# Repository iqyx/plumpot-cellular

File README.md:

plumpot-cellular
===================

A plumpot series base board with a sub-1GHz radio and a 2.5G cellular modem

Features
--------------------

- half-length, half-width form factor (80x50mm)
- mounting holes for half-length half-width and half-length quarter-width extension boards
- two extension bus connectors (UXB1 compatible - multidrop half-duplex SPI bus, I2C bus, wakeup request, interrupt request and 5V power)
- AX5243 sub-1GHz radio module with a 50ohm MMCX antenna connector
- Quectel M66 2.5G GPRS/EDGE cellular modem with a 50ohm MMCX antenna connector and network activity LED indicators
- 6-60Vin power supply step down regulator for providing system and bus power (5V, 0.2A)
- micro-B USB port with a CP2101 serial to USB bridge (console access and power input)
- RTC with a CR1220 lithium coin cell backup

The board is developed as an open source hardware using tools freely available for non-
commercial usage. It is able to run free and non-free commercial software without any
restrictions. It is not locked to a specific firmware and contains a standard 10-pin Cortex Debug
connector. A multitude of free and commercial development tools exist to develop and modify the
firmware for the board.

History
----------------

This is a uNodeX form-factor version of the qNode4 board (hence the previous name "unodex-connect-42").

I accepted a set of rules for board design, sizes, mounting types and board communication
to ease the development of new hardware. Such hardware could be easily connected together
to form wireless nodes for IoT/IoM and similar usages and enables you to do data acquisition,
data forwarding/communication, control, etc. I started to call this platform "uNodeX"
(micro node - extendable).

This is a rework of the previous qNode4 board to be compatible with the uNodeX platform,
with a slightly modified hardware:

- step-up converter for battery charging is removed
- RF connectors are changed to MMCX
- uNodeX bus connectors are added
- board dimensions are changed to 50x80mm (uNodeX half-width, half-depth)
- CP2102 USB to serial converter for console access
- VBUS power oring controller for uNodeX bus
- 6-60VDC step-down converter is added
- temperature sensor is removed

The board includes only a reduced set of hardware to fulfill the following requirements:

- to be a mainboard for HWHD or QWHD cards
- to provide power for them
- to enable them to communicate over the air (uMesh stack or GPRS/EDGE)

I started to call this board "plumpot" as it is mainly used to run the plumCore firmware.

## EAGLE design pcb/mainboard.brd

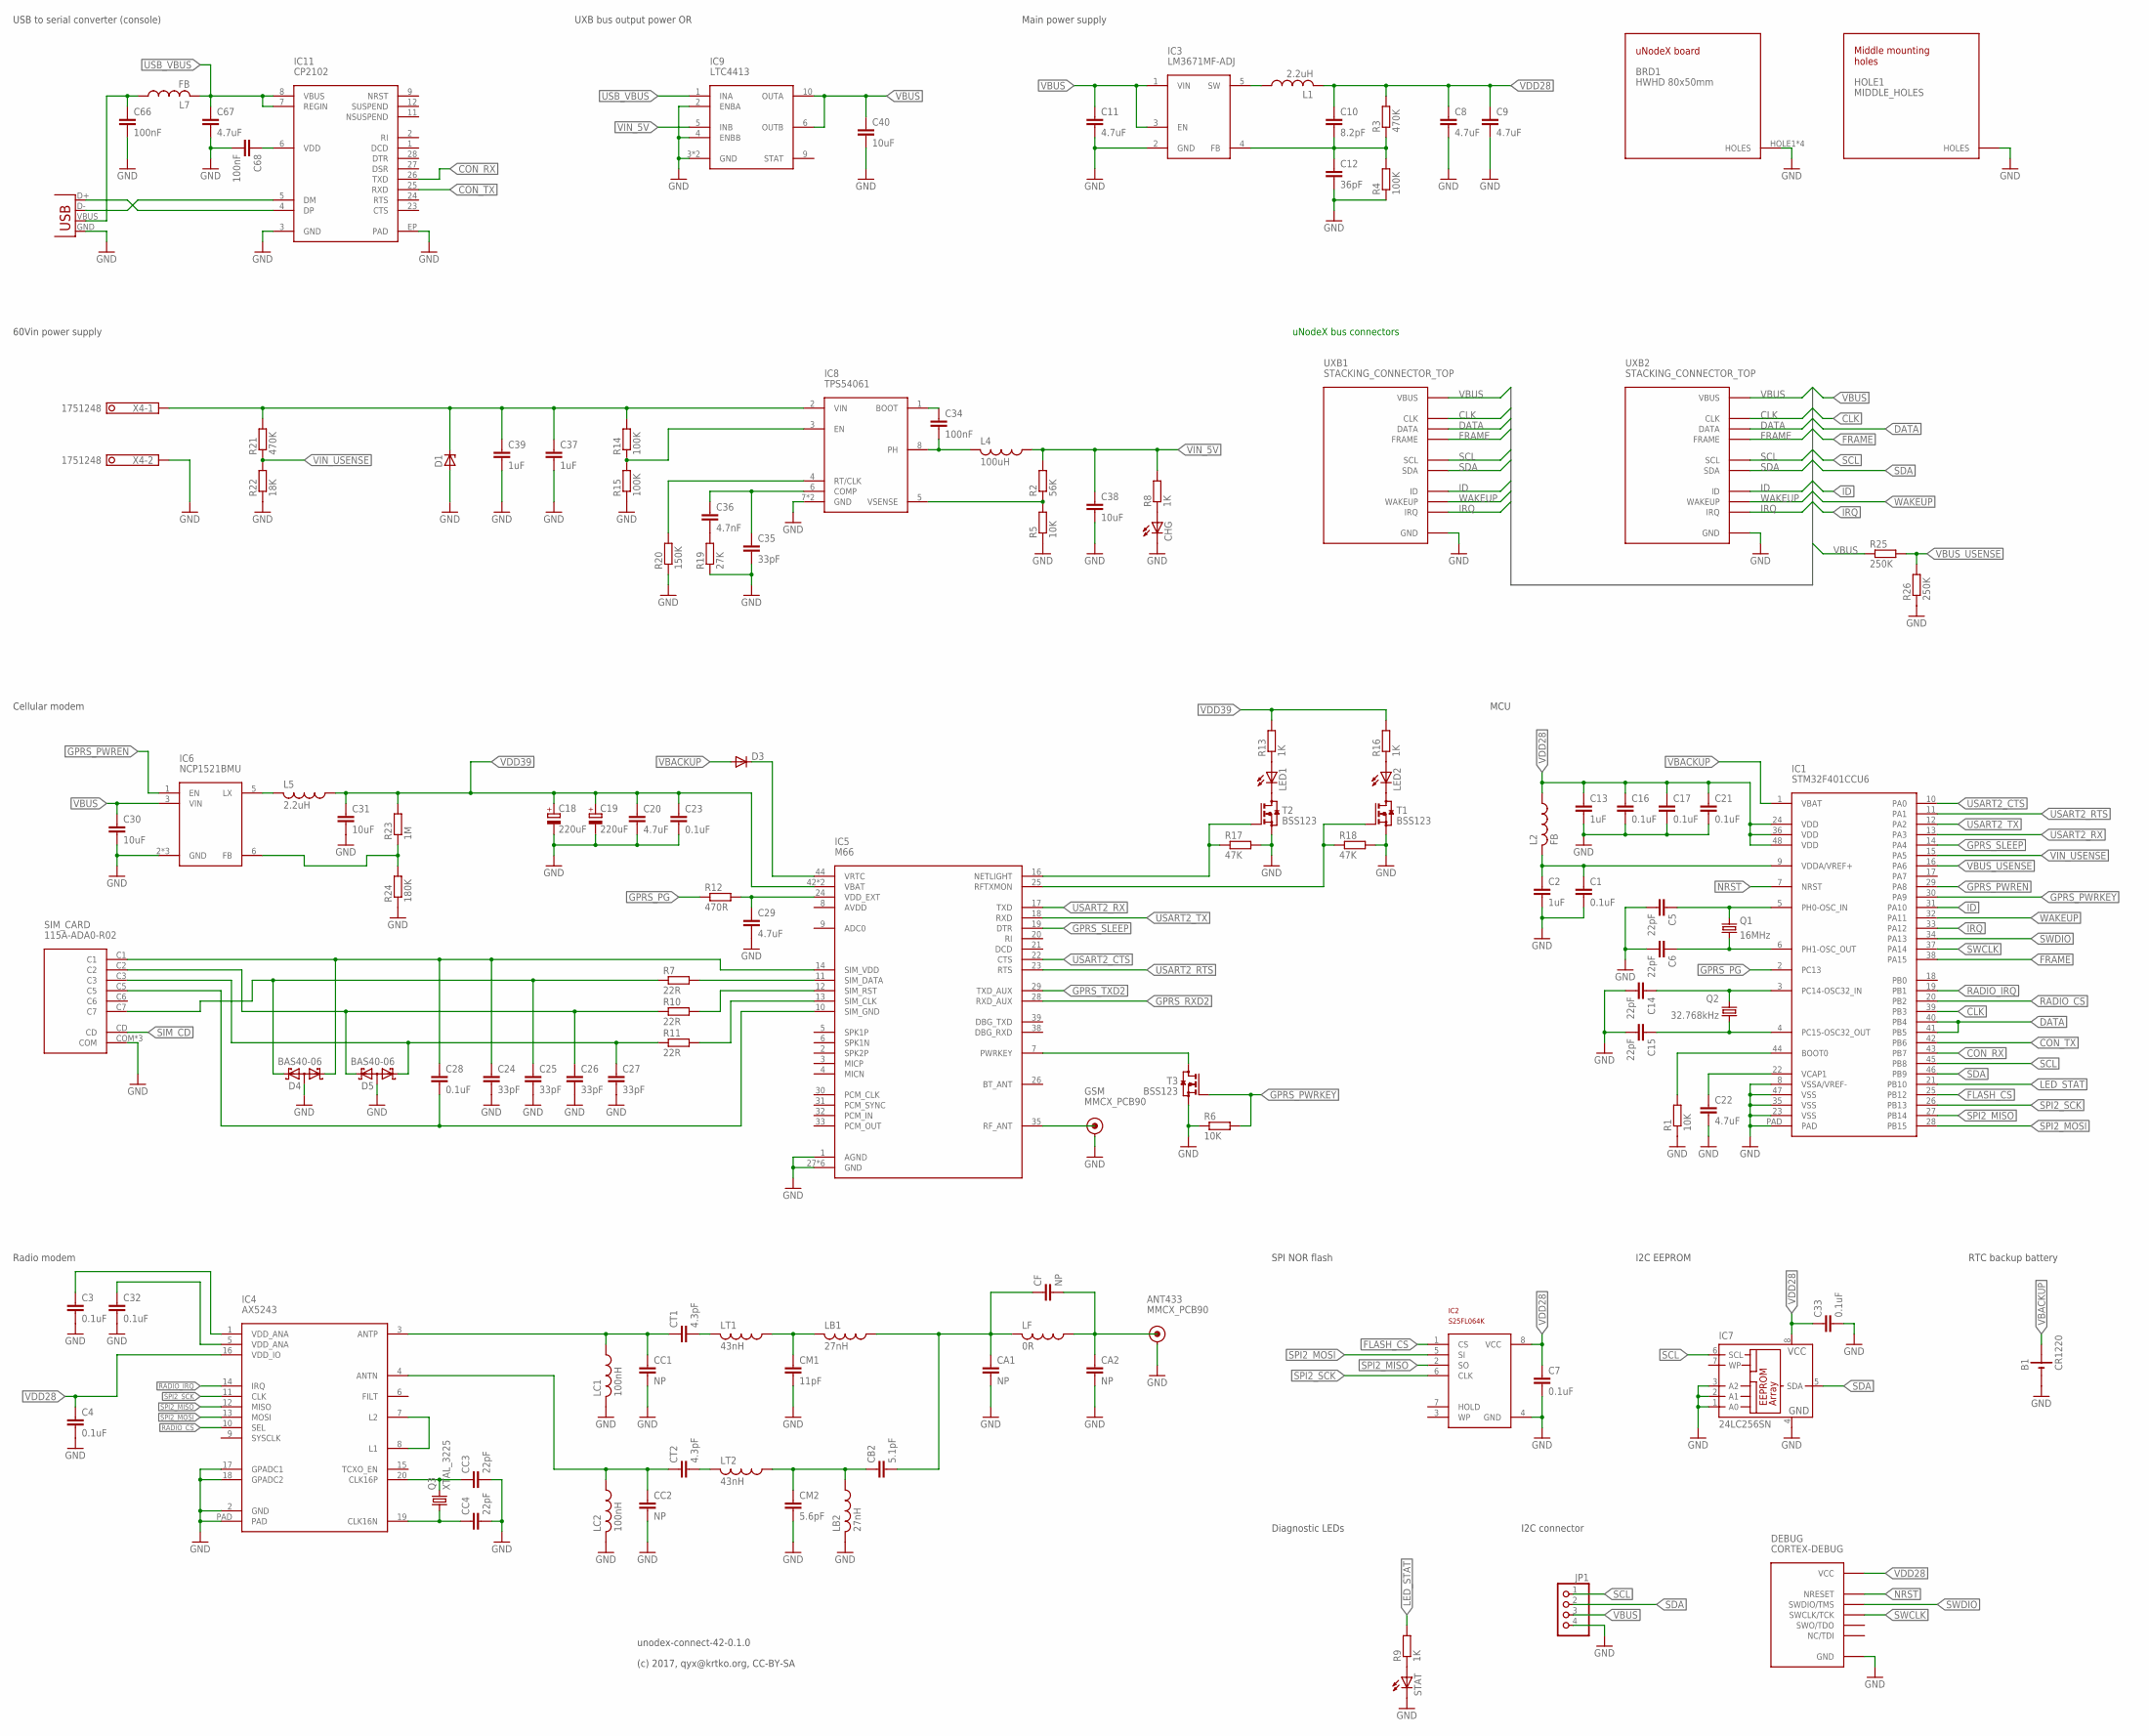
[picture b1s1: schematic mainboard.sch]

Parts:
ANT433: MMCX_PCB90; MMCX_PCB_90
B1: CR1220; CONNFLY_CR1220
BRD1: HWHD 80x50mm; HWHD_SHARP_CORNERS
C1, C3, C4, C7, C16, C17, C21, C23, C28, C32, C33: 0.1uF; C0603
C2, C13: 1uF; C0603
C5, C6, C14, C15: 22pF; C0603
C8, C9, C11, C20, C29, C67: 4.7uF; C0805
C10: 8.2pF; C0603
C12: 36pF; C0603
C18, C19: 220uF; PANASONIC_D
C22: 4.7uF; C0603
C24, C25, C26, C27, C35: 33pF; C0603
C30, C31, C38: 10uF; C1206
C34, C66, C68: 100nF; C0603
C36: 4.7nF; C0603
C37, C39: 1uF; C1206
C40: 10uF; C0805
CA1, CA2: NP; C0603
CB2: 5.1pF; C0603
CC1, CC2: NP; C0603
CC3, CC4: 22pF; C0603
CF: NP; C0603
CHG: LEDCHIPLED_0805; CHIPLED_0805
CM1: 11pF; C0603
CM2: 5.6pF; C0603
CT1, CT2: 4.3pF; C0603
D1: ZENER-DIODESMB; SMB
D3: DIODE-SOD123; SOD123
D4, D5: BAS40-06; SOT23
DEBUG: CORTEX-DEBUG
GSM: MMCX_PCB90; MMCX_PCB_90
HOLE1: MIDDLE_HOLES
IC1: STM32F401CCU6; UFQFPN48
IC2: S25FL064K; SO-08M
IC3: LM3671MF-ADJ; SOT23-5
IC4: AX5243; QFN20
IC5: M66
IC6: NCP1521BMU; UDFN6
IC7: 24LC256SN; SO-08
IC8: TPS54061; WSON8
IC9: LTC4413; DFN10
IC11: CP2102; QFN28
JP1: PINHD-1X4; 1X04
L1, L5: 2.2uH; L2825P
L2, L7: FB; L2012C
L4: 100uH; L5650M
LB1, LB2: 27nH; L2012C
LC1, LC2: 100nH; L2012C
LED1, LED2: LEDCHIP-LED0805; CHIP-LED0805
LF: 0R; L2012C
LT1, LT2: 43nH; L2012C
Q1: 16MHz; XTAL_3225
Q2: 32.768kHz; TC26H
Q3: XTAL_3225
R1, R5, R6: 10K; R0603
R2: 56K; R0603
R3, R21: 470K; R0603
R4, R14, R15: 100K; R0603
R7, R10, R11: 22R; R0603
R8, R9, R13, R16: 1K; R0603
R12: 470R; R0603
R17, R18: 47K; R0603
R19: 27K; R0603
R20: 150K; R0603
R22: 18K; R0603
R23: 1M; R0603
R24: 180K; R0603
R25, R26: 250K; R0603
SIM_CARD: 115A-ADA0-R02
STAT: LEDCHIPLED_0805; CHIPLED_0805
T1, T2, T3: BSS123; SOT23
UXB1, UXB2: STACKING_CONNECTOR_TOP; HAR-FLEX-TOP-12P
X4: 1751248
X5: USB-MICROB

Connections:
ANT: ANT433.C (CENTER), CA2.1, CF.2, LF.1
ANTN: CC2.1, CT2.1, IC4.4 (ANTN), LC2.1
ANTP: CC1.1, CT1.1, IC4.3 (ANTP), LC1.1
CLK: IC1.39 (PB3), UXB1.CLK, UXB2.CLK
CON_RX: IC1.43 (PB7), IC11.26 (TXD)
CON_TX: IC1.42 (PB6), IC11.25 (RXD)
DATA: IC1.40 (PB4), IC1.41 (PB5), UXB1.DATA, UXB2.DATA
FLASH_CS: IC1.25 (PB12), IC2.1 (CS)
FRAME: IC1.38 (PA15), UXB1.FRAME, UXB2.FRAME
GND: ANT433.S1 (SHIELD), ANT433.S2 (SHIELD), ANT433.S3 (SHIELD), ANT433.S4 (SHIELD), B1.NEG (-), BRD1.HOLE1, BRD1.HOLE2, BRD1.HOLE3, BRD1.HOLE4, C1.2, C2.2, C3.2, C4.2, C5.2, C6.2, C7.2, C8.2, C9.2, C11.2, C12.2, C13.2, C14.2, C15.2, C16.2, C17.2, C18.-, C19.-, C20.2, C21.2, C22.2, C23.2, C24.2, C25.2, C26.2, C27.2, C29.2, C30.2, C31.2, C32.2, C33.2, C35.2, C37.2, C38.2, C39.2, C40.2, C66.2, C67.2, C68.2, CA1.2, CA2.2, CC1.2, CC2.2, CC3.2, CC4.2, CHG.C, CM1.2, CM2.2, D1.A, D4.3 (AA), D5.3 (AA), DEBUG.GND1 (GND), DEBUG.GND2 (GND), DEBUG.GND_DETECT (GND), GSM.S1 (SHIELD), GSM.S2 (SHIELD), GSM.S3 (SHIELD), GSM.S4 (SHIELD), HOLE1.P$1, HOLE1.P$2, HOLE1.P$3, HOLE1.P$4, IC1.8 (VSSA/VREF-), IC1.23 (VSS), IC1.35 (VSS), IC1.47 (VSS), IC1.PAD, IC2.4 (GND), IC3.2 (GND), IC4.2 (GND), IC4.17 (GPADC1), IC4.18 (GPADC2), IC4.PAD, IC5.1 (AGND), IC5.27 (GND), IC5.34 (GND), IC5.36 (GND), IC5.37 (GND), IC5.40 (GND), IC5.41 (GND), IC6.2 (GND), IC6.4 (GND), IC6.PAD (GND), IC7.1 (A0), IC7.2 (A1), IC7.3 (A2), IC7.4 (GND), IC8.7 (GND), IC8.PAD (GND), IC9.2 (ENBA), IC9.3 (GND), IC9.4 (ENBB), IC9.PAD (GND), IC11.3 (GND), IC11.EP (PAD), JP1.4, LB2.2, LC1.2, LC2.2, R1.1, R4.1, R5.1, R6.1, R15.1, R17.2, R18.2, R19.1, R20.1, R22.1, R24.1, R26.1, SIM_CARD.COM, SIM_CARD.H1 (COM), SIM_CARD.H2 (COM), STAT.C, T1.2 (S), T2.2 (S), T3.2 (S), UXB1.GND1 (GND), UXB1.GND2 (GND), UXB1.GND3 (GND), UXB1.H1 (GND), UXB1.H2 (GND), UXB1.H3 (GND), UXB1.H4 (GND), UXB2.GND1 (GND), UXB2.GND2 (GND), UXB2.GND3 (GND), UXB2.H1 (GND), UXB2.H2 (GND), UXB2.H3 (GND), UXB2.H4 (GND), X4.2, X5.GND
GPRS_PG: IC1.2 (PC13), R12.1
GPRS_PWREN: IC1.29 (PA8), IC6.1 (EN)
GPRS_PWRKEY: IC1.30 (PA9), R6.2, T3.1 (G)
GPRS_RXD2: IC5.28 (RXD_AUX)
GPRS_SLEEP: IC1.14 (PA4), IC5.19 (DTR)
GPRS_TXD2: IC5.29 (TXD_AUX)
ID: IC1.31 (PA10), UXB1.ID, UXB2.ID
IRQ: IC1.33 (PA12), UXB1.IRQ, UXB2.IRQ
LED_STAT: IC1.21 (PB10), R9.2
unnamed: CHG.A, R8.1
unnamed: C1.1, C2.1, IC1.9 (VDDA/VREF+), L2.2
unnamed: IC3.5 (SW), L1.1
unnamed: C5.1, IC1.5 (PH0-OSC_IN), Q1.3 (2)
unnamed: C22.1, IC1.22 (VCAP1)
unnamed: R9.1, STAT.A
unnamed: C10.2, C12.1, IC3.4 (FB), R3.1, R4.2
unnamed: C6.1, IC1.6 (PH1-OSC_OUT), Q1.1
unnamed: C14.1, IC1.3 (PC14-OSC32_IN), Q2.2
unnamed: C15.1, IC1.4 (PC15-OSC32_OUT), Q2.1
unnamed: IC1.44 (BOOT0), R1.2
unnamed: D3.C, IC5.44 (VRTC)
unnamed: IC5.25 (RFTXMON), R18.1, T1.1 (G)
unnamed: C34.2, IC8.8 (PH), L4.2
unnamed: C34.1, IC8.1 (BOOT)
unnamed: IC8.5 (VSENSE), R2.1, R5.2
unnamed: GSM.C (CENTER), IC5.35 (RF_ANT)
unnamed: IC5.7 (PWRKEY), T3.3 (D)
unnamed: LED1.C, T2.3 (D)
unnamed: C29.1, IC5.24 (VDD_EXT), R12.2
unnamed: LED2.C, T1.3 (D)
unnamed: LED1.A, R13.1
unnamed: LED2.A, R16.1
unnamed: IC5.16 (NETLIGHT), R17.1, T2.1 (G)
unnamed: IC11.4 (DP), X5.D+
unnamed: IC11.5 (DM), X5.D-
unnamed: CA1.1, CB2.2, CF.1, LB1.1, LF.2
unnamed: CT1.2, LT1.2
unnamed: CM1.1, LB1.2, LT1.1
unnamed: CT2.2, LT2.2
unnamed: CB2.1, CM2.1, LB2.1, LT2.1
unnamed: C3.1, IC4.1 (VDD_ANA)
unnamed: IC4.7 (L2), IC4.8 (L1)
unnamed: C32.1, IC4.5 (VDD_ANA)
unnamed: CC3.1, IC4.20 (CLK16P), Q3.3 (2)
unnamed: CC4.1, IC4.19 (CLK16N), Q3.1
unnamed: C36.2, R19.2
unnamed: C35.1, C36.1, IC8.6 (COMP)
unnamed: IC8.4 (RT/CLK), R20.2
unnamed: IC6.5 (LX), L5.2
unnamed: C37.1, C39.1, D1.C, IC8.2 (VIN), R14.2, R21.2, X4.1
unnamed: IC8.3 (EN), R14.1, R15.2
unnamed: IC6.6 (FB), R23.1, R24.2
unnamed: C66.1, L7.1, X5.VBUS
unnamed: C68.1, IC11.6 (VDD)
NRST: DEBUG.NRESET, IC1.7 (NRST)
RADIO_CS: IC1.20 (PB2), IC4.10 (SEL)
RADIO_IRQ: IC1.19 (PB1), IC4.14 (IRQ)
SCL: IC1.45 (PB8), IC7.6 (SCL), JP1.1, UXB1.SCL, UXB2.SCL
SDA: IC1.46 (PB9), IC7.5 (SDA), JP1.2, UXB1.SDA, UXB2.SDA
SIM_CD: SIM_CARD.CD
SIM_CLK: IC5.13 (SIM_CLK), R11.2
SIM_CLK_R: C27.1, D5.1 (K1), R11.1, SIM_CARD.C3
SIM_DATA: IC5.11 (SIM_DATA), R7.2
SIM_DATA_R: C25.1, D4.2 (K2), R7.1, SIM_CARD.C7
SIM_GND: C28.2, IC5.10 (SIM_GND), SIM_CARD.C5
SIM_RST: IC5.12 (SIM_RST), R10.2
SIM_RST_R: C26.1, D5.2 (K2), R10.1, SIM_CARD.C2
SIM_VDD: C24.1, C28.1, D4.1 (K1), IC5.14 (SIM_VDD), SIM_CARD.C1
SPI2_MISO: IC1.27 (PB14), IC2.2 (SO), IC4.12 (MISO)
SPI2_MOSI: IC1.28 (PB15), IC2.5 (SI), IC4.13 (MOSI)
SPI2_SCK: IC1.26 (PB13), IC2.6 (CLK), IC4.11 (CLK)
SWCLK: DEBUG.SWCLK/TCK, IC1.37 (PA14)
SWDIO: DEBUG.SWDIO/TMS, IC1.34 (PA13)
USART2_CTS: IC1.10 (PA0), IC5.22 (CTS)
USART2_RTS: IC1.11 (PA1), IC5.23 (RTS)
USART2_RX: IC1.13 (PA3), IC5.17 (TXD)
USART2_TX: IC1.12 (PA2), IC5.18 (RXD)
USB_VBUS: C67.1, IC9.1 (INA), IC11.7 (REGIN), IC11.8 (VBUS), L7.2
VBACKUP: B1.POS (+), D3.A, IC1.1 (VBAT)
VBUS: C11.1, C30.1, C40.1, IC3.1 (VIN), IC3.3 (EN), IC6.3 (VIN), IC9.6 (OUTB), IC9.10 (OUTA), JP1.3, R25.1, UXB1.VBUS, UXB2.VBUS
VBUS_USENSE: IC1.16 (PA6), R25.2, R26.2
VDD28: C4.1, C7.1, C8.1, C9.1, C10.1, C13.1, C16.1, C17.1, C21.1, C33.1, DEBUG.VCC, IC1.24 (VDD), IC1.36 (VDD), IC1.48 (VDD), IC2.8 (VCC), IC4.16 (VDD_IO), IC7.8 (VCC), L1.2, L2.1, R3.2
VDD39: C18.+, C19.+, C20.1, C23.1, C31.1, IC5.42 (VBAT), IC5.43 (VBAT), L5.1, R13.2, R16.2, R23.2
VIN_5V: C38.1, IC9.5 (INB), L4.1, R2.2, R8.2
VIN_USENSE: IC1.15 (PA5), R21.1, R22.2
WAKEUP: IC1.32 (PA11), UXB1.WAKEUP, UXB2.WAKEUP

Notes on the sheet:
SPI NOR flash
Diagnostic LEDs
MCU
uNodeX bus connectors
USB to serial converter (console)
UXB bus output power OR
Main power supply
60Vin power supply
Cellular modem
Radio modem
I2C connector
RTC backup battery
I2C EEPROM
unodex-connect-42-0.1.0
(c) 2017, qyx@krtko.org, CC-BY-SA

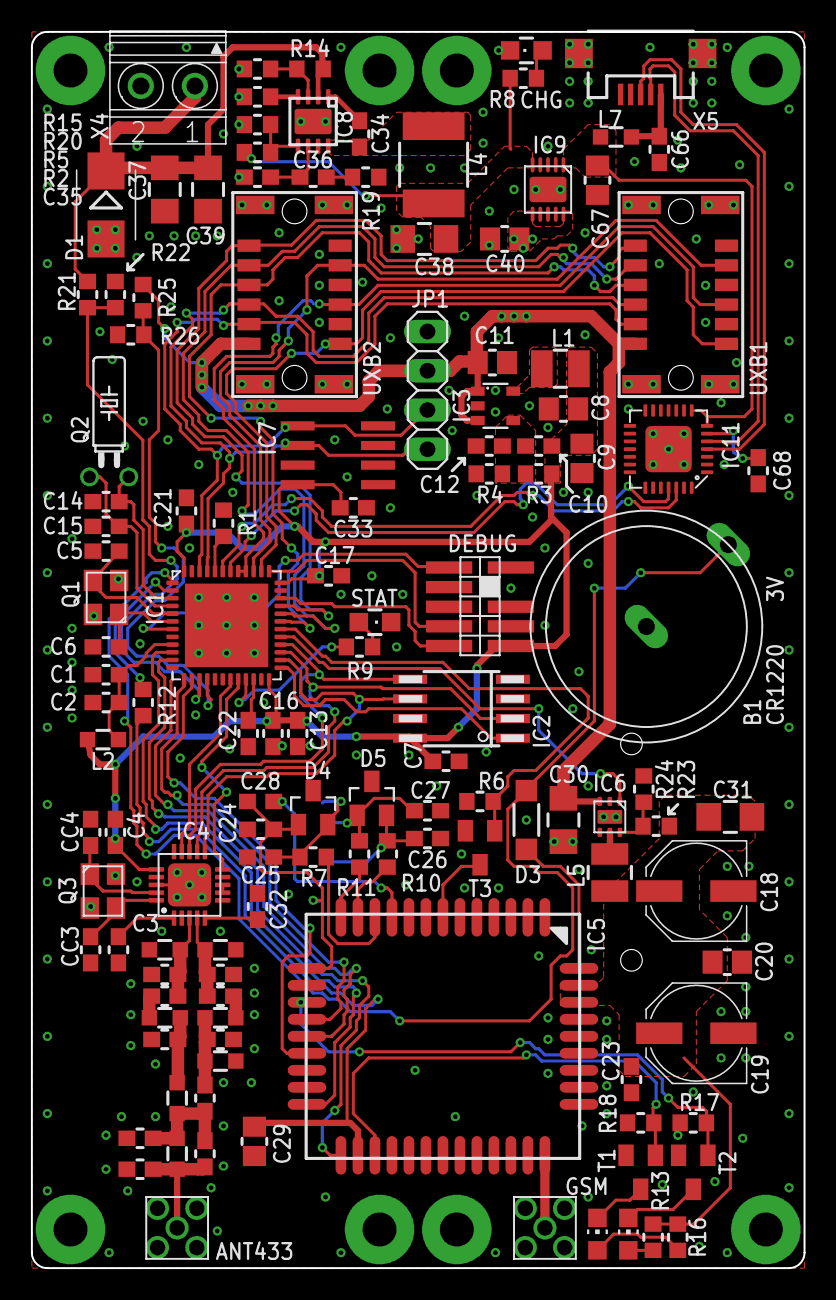
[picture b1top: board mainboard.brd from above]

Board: 2 copper layers, 50.0 x 80.0 mm, 129 parts (1 on the bottom side), 93 nets.

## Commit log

2017-10-31 Initialize the repository with .gitignore and README
2017-10-31 Add schematic and layout of the board
2017-10-31 Add generated Gerber outputs (for seeedstudio)
2017-10-31 Add board documentation draft
2018-11-09 Add a to-do list for the next board revision

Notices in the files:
pcb/mainboard.brd:
(c) qyx@krtko.org, CC-BY-SA
parts and their libraries:
SparkFun: Licensing: CC v3.0 Share-Alike You are welcome to use this library for commercial purposes.
